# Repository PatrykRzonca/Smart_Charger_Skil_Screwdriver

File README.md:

# Smart_Charger_Skil_Screwdriver
Private project for screwdriver

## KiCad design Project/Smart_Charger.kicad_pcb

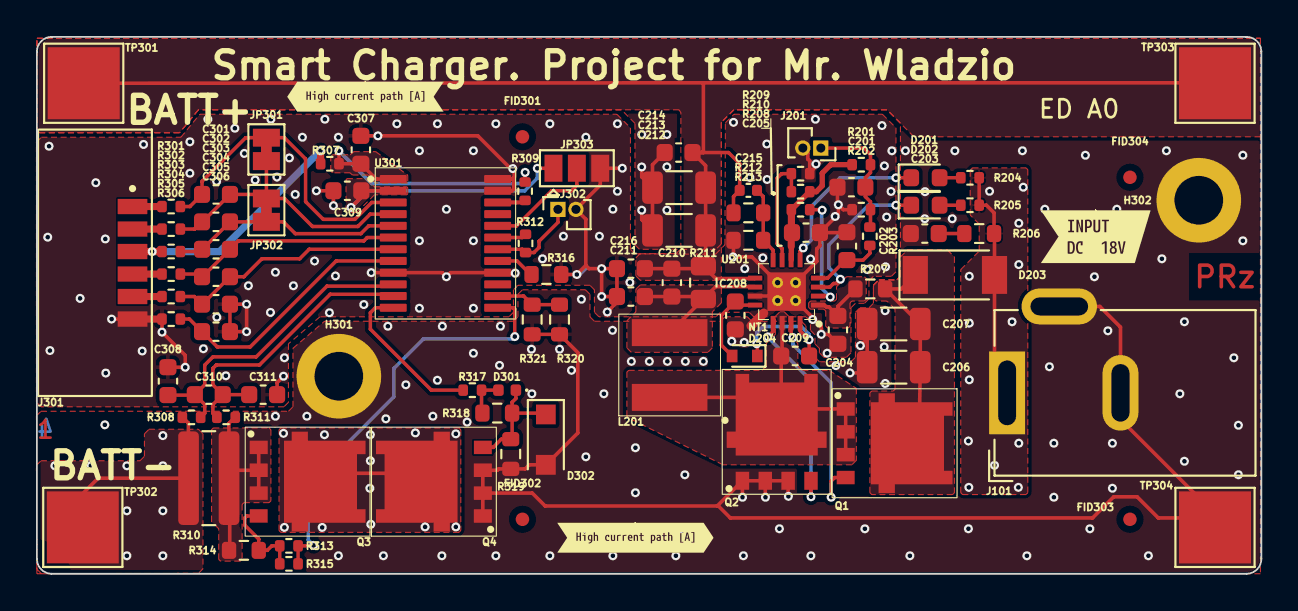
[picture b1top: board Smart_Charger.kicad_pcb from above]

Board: 4 copper layers, 68.0 x 29.8 mm, 95 parts (0 on the bottom side), 52 nets.

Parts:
C201, C202, C209, C210, C211, C216, C301, C302, C303, C304, C305, C306, C308, C310, C311: 100n; C_0603_1608Metric
C203: 2u2; C_0603_1608Metric
C204, C205, C208, C214, C307, C309: 1u; C_0603_1608Metric
C206, C207, C212, C213: 10u; C_1206_3216Metric
C215: 22p; C_0402_1005Metric
D201, D202: 5mA; D_0603_1608Metric
D203: RB088LAM-40TR; D_SOD-128
D204: RB501SM-30FHT2R; D_SOD-523
D301: D_Schottky; D_0402_1005Metric
D302: D_TVS; D_SOD-123F
FID301, FID302, FID303, FID304: Fiducial; Fiducial_0.75mm_Mask1.5mm
H301, H302: MountingHole_Pad; MountingHole_2.7mm_M2.5_DIN965_Pad
J101: Barrel_Jack_Switch; BarrelJack_GCT_DCJ200-10-A_Horizontal
J201, J302: Conn_01x02_Female; PinSocket_1x02_P1.00mm_Vertical
J301: 10114830-10106LF
JP301, JP302: SolderJumper_2_Bridged; SolderJumper-2_P1.3mm_Bridged_Pad1.0x1.5mm
JP303: SolderJumper_3_Open; SolderJumper-3_P1.3mm_Open_Pad1.0x1.5mm
L201: SRN5040TA-3R3M
NT1: NetTie_2; NetTie-2_SMD_Pad0.5mm
Q1, Q2, Q3, Q4: NTMFS5C468NLT1G; NTMFS5C468NLT1G_SO-8FL-4
R201, R202, R204, R205, R309, R312, R313, R315, R317: 10k; R_0402_1005Metric
R203: 150R; R_0402_1005Metric
R206: 2R; R_0603_1608Metric
R207: 10R; R_0603_1608Metric
R208: 0R; R_0402_1005Metric
R209: 200k; R_0402_1005Metric
R210: 45k3; R_0402_1005Metric
R211: 15m; R_0805_2012Metric
R212: 715k; R_0603_1608Metric
R213, R316: 100k; R_0603_1608Metric
R301, R302, R303, R304, R305, R306, R307: 1k8; R_0402_1005Metric
R308, R311: 60R4; R_0402_1005Metric
R310: 5mR; R_1020_2550Metric
R314, R318, R320, R321: 1M; R_0603_1608Metric
R319: 3M3; R_0603_1608Metric
TP301, TP302, TP303, TP304: TestPoint; TestPoint_Pad_4.0x4.0mm
U201: BQ24600RVAT; BQ24600RVAT_VQFN-16
U301: BQ7791502PWR; BQ7791502PWR_TSSOP-24
kibuzzard-623A0E03: G***; kibuzzard-623A0E03
kibuzzard-623A40DC: G***; kibuzzard-623A40DC
kibuzzard-623A4100: G***; kibuzzard-623A4100

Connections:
+12V: J301.3, R303.1, R307.1
/BQ24600RVAT/ADAPTER+: D203.2 (A), J101.1, R204.2, R205.2, R206.2
/BQ24600RVAT/BQ24600RVAT_BTST: C209.1, D204.1 (K), U201.16 (BTST)
/BQ24600RVAT/BQ24600RVAT_FB: C215.1, R212.1, R213.2, U201.8 (VFB)
/BQ24600RVAT/BQ24600RVAT_HIDRV: Q1.4 (G), U201.15 (HIDRV)
/BQ24600RVAT/BQ24600RVAT_ISET: R209.1, R210.2, U201.7 (ISET)
/BQ24600RVAT/BQ24600RVAT_LODRV: Q2.4 (G), U201.13 (LODRV)
/BQ24600RVAT/BQ24600RVAT_PH: C209.2, L201.1, Q1.1 (S1), Q1.2 (S2), Q1.3 (S3), Q2.5 (D), U201.14 (PH)
/BQ24600RVAT/BQ24600RVAT_PWR: C206.2, C207.2, D203.1 (K), Q1.5 (D), R207.2
/BQ24600RVAT/BQ24600RVAT_REGN: C208.2, D204.2 (A), U201.12 (REGN)
/BQ24600RVAT/BQ24600RVAT_SR_N: C210.2, C212.2, C213.2, C214.2, C215.2, C216.2, R211.2, R212.2, TP301.1, TP303.1, U201.9 (SRN)
/BQ24600RVAT/BQ24600RVAT_SR_P: C210.1, C211.2, L201.2, R211.1, U201.10 (SRP)
/BQ24600RVAT/BQ24600RVAT_STAT: D202.1 (K), U201.3 (STAT)
/BQ24600RVAT/BQ24600RVAT_TS: C202.2, R203.1, U201.4 (TS)
/BQ24600RVAT/BQ24600RVAT_~PG: D201.1 (K), U201.5 (~PG)
/BQ24600RVAT/TS: C201.2, J201.1, R201.2, R202.2, R203.2
/BQ24600RVAT/VCC: C204.2, R207.1, U201.1 (VCC)
/BQ7791502PWR/AVDD: C309.2, JP303.1 (A), U301.2 (AVDD)
/BQ7791502PWR/BATT-: R308.1, R310.1, TP302.1
/BQ7791502PWR/BQ7791502PWR_CCFG: JP303.2 (C), U301.20 (CCFG)
/BQ7791502PWR/BQ7791502PWR_CHG: R313.2, R315.2, U301.13 (CHG)
/BQ7791502PWR/BQ7791502PWR_DSG: R317.2, U301.12 (DSG)
/BQ7791502PWR/BQ7791502PWR_LD: R320.2, R321.2, U301.14 (LD)
/BQ7791502PWR/BQ7791502PWR_OCDP: R316.2, U301.17 (OCDP)
/BQ7791502PWR/BQ7791502PWR_PRES: R309.2, U301.22 (PRES)
/BQ7791502PWR/BQ7791502PWR_SR_N: C310.1, C311.2, R311.2, U301.11 (SRN)
/BQ7791502PWR/BQ7791502PWR_SR_P: C308.2, C310.2, R308.2, U301.10 (SRP)
/BQ7791502PWR/BQ7791502PWR_VCC0: C306.1, R306.2, U301.8 (VC0)
/BQ7791502PWR/BQ7791502PWR_VCC1: C304.1, C305.2, R305.2, U301.7 (VC1)
/BQ7791502PWR/BQ7791502PWR_VCC2: C303.1, C304.2, R304.2, U301.6 (VC2)
/BQ7791502PWR/BQ7791502PWR_VCC3: C302.1, C303.2, JP302.1 (A), R303.2, U301.5 (VC3)
/BQ7791502PWR/BQ7791502PWR_VCC4: C301.1, C302.2, JP301.1 (A), JP302.2 (B), R302.2, U301.4 (VC4)
/BQ7791502PWR/BQ7791502PWR_VCC5: C301.2, JP301.2 (B), R301.2, U301.3 (VC5)
/BQ7791502PWR/TS: J302.1, R312.2, U301.18 (TS)
/BQ7791502PWR/VDD: C307.2, R307.2, R309.1, U301.1 (VDD)
/BQ7791502PWR/VTB: R312.1, U301.19 (VTB)
GND: C201.1, C202.1, C204.1, C205.1, C211.1, C216.1, C305.1, C306.2, C307.1, C308.1, C309.1, C311.1, J201.2, J301.6, J302.2, JP303.3 (B), NT1.2, R202.1, R210.1, R213.1, R306.1, R316.1, U201.11 (GND), U201.17 (Exp_Pad), U301.9 (VSS), U301.16 (CBI), U301.23 (CTRC), U301.24 (CTRD)
GNDPWR: C203.1, C206.1, C207.1, C208.1, C212.1, C213.1, C214.1, D302.2 (A2), H301.1, H302.1, J101.2, J101.3, NT1.1, Q2.1 (S1), Q2.2 (S2), Q2.3 (S3), Q4.1 (S1), Q4.2 (S2), Q4.3 (S3), R319.1, R320.1, R321.1, TP304.1
unnamed: C203.2, R206.1
unnamed: D201.2 (A), R204.1
unnamed: D202.2 (A), R205.1
unnamed: D301.1 (K), D302.1 (A1), Q4.4 (G), R318.1, R319.2
unnamed: D301.2 (A), R317.1, R318.2
unnamed: J301.1, R301.1
unnamed: J301.2, R302.1
unnamed: J301.4, R304.1
unnamed: J301.5, R305.1
unnamed: Q3.1 (S1), Q3.2 (S2), Q3.3 (S3), R310.2, R311.1, R314.1
unnamed: Q3.4 (G), R313.1, R314.2, R315.1
unnamed: Q3.5 (D), Q4.5 (D)
unnamed: R208.1, U201.2 (CE)
VREF: C205.2, R201.1, R208.2, R209.2, U201.6 (VREF)

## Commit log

2022-03-27 First commit for fixing
2022-03-27 Moved RefDes TP304 and FID303 to be not on the same place
